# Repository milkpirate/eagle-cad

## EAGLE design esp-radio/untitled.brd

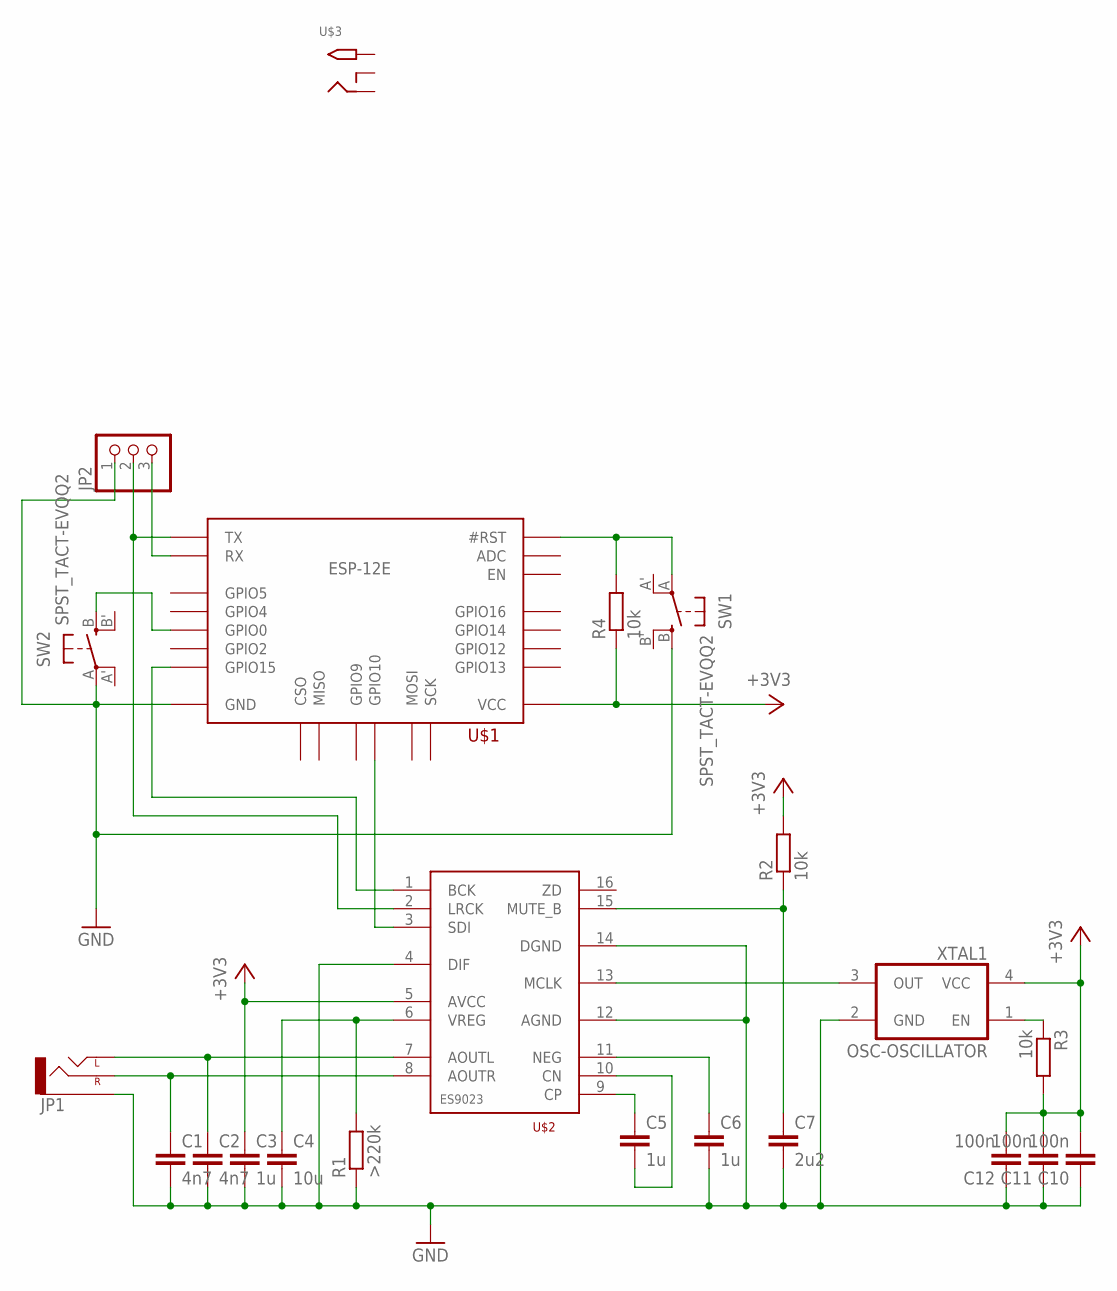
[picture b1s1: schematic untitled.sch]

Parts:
C1, C2: 4n7; C0805K
C3, C5, C6: 1u; C0805K
C4: 10u; C0805K
C7: 2u2; C0805K
C10, C11, C12: 100n; C0805K
JP1: AUDIO-JACKPIN-HOLES; AUDIO-JACK-HOLES
JP2: PINHD-1X3; 1X03
R1: >220k; M0805
R2, R3, R4: 10k; M0805
SW1, SW2: SPST_TACT-EVQQ2; EVQ-Q2
U$1: ESP-07/12_ESP-12E; ESP-07/12
U$2: ES9023-SMD; SOP16
U$3: 2.1MMJACKTHM; PJ-102A
XTAL1: OSC-OSCILLATOR; OSCILLATOR_7X5_SMD

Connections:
+3V3: C3.1, C10.2, C11.2, C12.2, R2.2, R3.2, R4.1, U$1.VCC, U$2.5 (AVCC), XTAL1.4 (VCC)
GND: C1.2, C2.2, C3.2, C4.2, C6.2, C7.2, C10.1, C11.1, C12.1, JP1.GND (SLEEVE), JP2.1, R1.1, SW1.B (S), SW2.A, U$1.GND, U$2.4 (DIF), U$2.12 (AGND), U$2.14 (DGND), XTAL1.2 (GND)
unnamed: R3.1, XTAL1.1 (EN)
unnamed: R4.2, SW1.A, U$1.REST (#RST)
unnamed: C4.1, R1.2, U$2.6 (VREG)
unnamed: C5.1, U$2.9 (CP)
unnamed: C5.2, U$2.10 (CN)
unnamed: C6.1, U$2.11 (NEG)
unnamed: C7.1, R2.1, U$2.15 (MUTE_B)
unnamed: SW2.B (S), U$1.GPIO0
unnamed: U$1.GPIO15, U$2.1 (BCK)
unnamed: C1.1, JP1.R+ (RIGHT), U$2.8 (AOUTR)
unnamed: C2.1, JP1.L1- (LEFT), JP1.L2- (LEFT), U$2.7 (AOUTL)
unnamed: JP2.2, U$1.TXD0 (TX), U$2.2 (LRCK)
unnamed: JP2.3, U$1.RXD0 (RX)
unnamed: U$1.GPIO10, U$2.3 (SDI)
unnamed: U$2.13 (MCLK), XTAL1.3 (OUT)

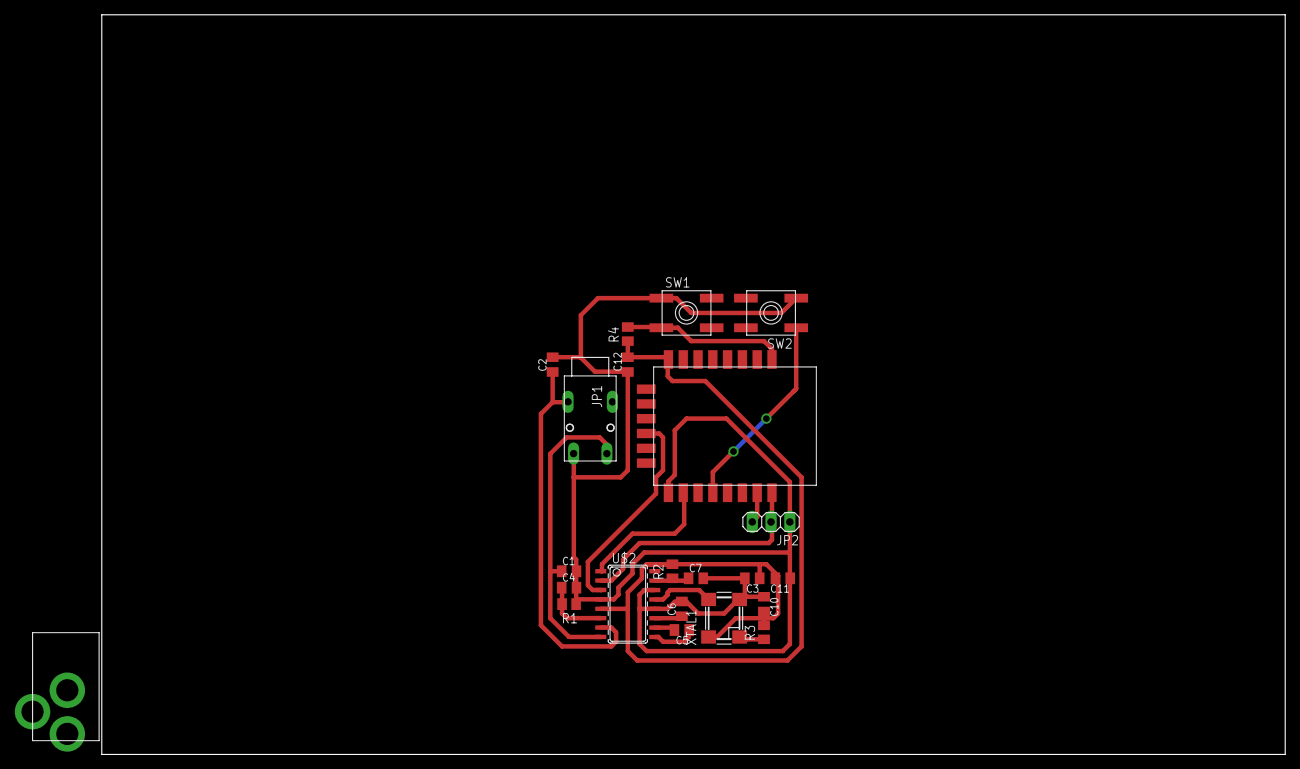
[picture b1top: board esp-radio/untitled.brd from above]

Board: 2 copper layers, 160.0 x 100.0 mm, 22 parts (0 on the bottom side), 17 nets.

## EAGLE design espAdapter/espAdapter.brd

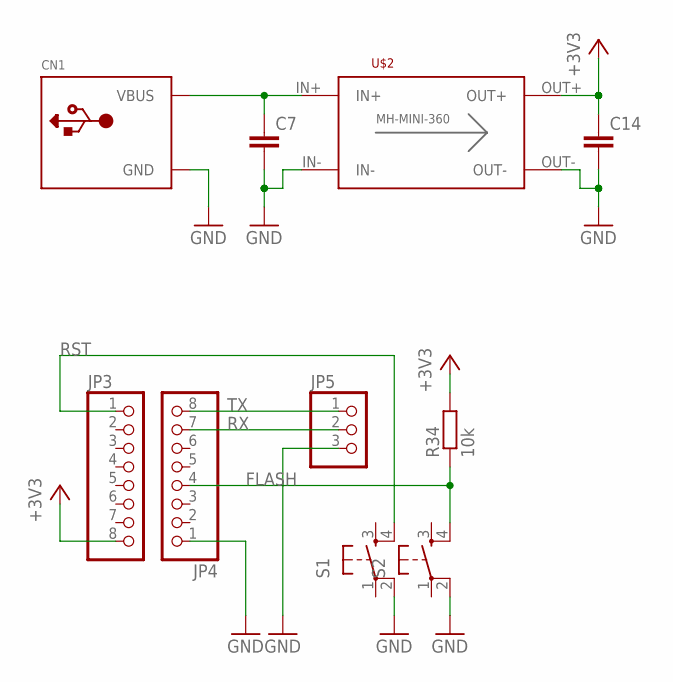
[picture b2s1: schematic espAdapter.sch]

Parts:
C7, C14: C-EU025-025X050; C025-025X050
CN1: USBPWR-ONLY; USB-MINIB-THM
JP3, JP4: PINHD-1X8; 1X08
JP5: PINHD-1X3; 1X03
R34: 10k; 0204/7
S1, S2: TAC_SWITCHPTH; TACTILE-PTH
U$2: DC-DC_CONV_MINISTD; DC-DC_CONV_MINI

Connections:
+3V3: C14.1, JP3.8, R34.2, U$2.OUT+
FLASH: JP4.4, R34.1, S2.4
GND: C7.2, C14.2, CN1.GND, CN1.GND1 (GND), CN1.GND2 (GND), CN1.GND3 (GND), CN1.GND4 (GND), JP4.1, JP5.3, S1.2, S2.2, U$2.IN-, U$2.OUT-
unnamed: C7.1, CN1.VBUS, U$2.IN+
RST: JP3.1, S1.4
RX: JP4.7, JP5.2
TX: JP4.8, JP5.1

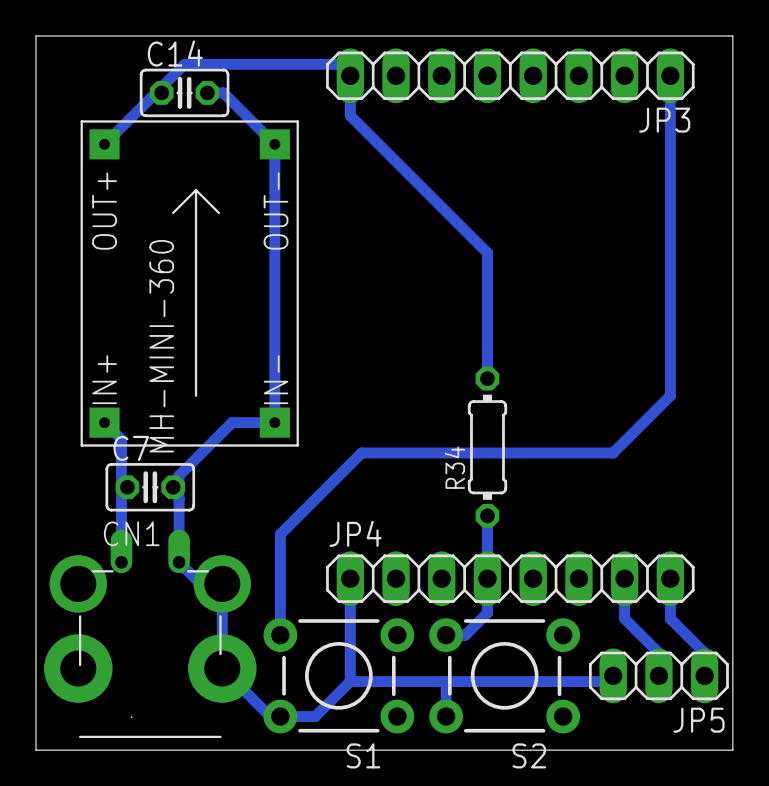
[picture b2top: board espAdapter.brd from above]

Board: 2 copper layers, 38.7 x 39.7 mm, 10 parts (0 on the bottom side), 7 nets.

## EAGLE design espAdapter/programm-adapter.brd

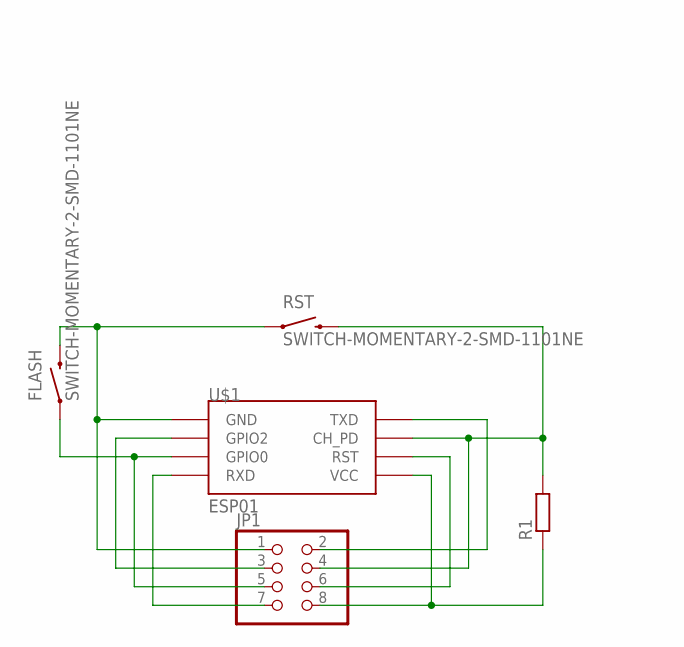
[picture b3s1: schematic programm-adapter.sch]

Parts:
FLASH: SWITCH-MOMENTARY-2-SMD-1101NE; TACTILE-SWITCH-1101NE
JP1: PINHD-2X4; 2X04
R1: R-EU_M0805; M0805
RST: SWITCH-MOMENTARY-2-SMD-1101NE; TACTILE-SWITCH-1101NE
U$1: ESP01

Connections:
GND: FLASH.2, JP1.1, RST.1, U$1.GND
unnamed: JP1.6, U$1.RST
unnamed: JP1.4, R1.2, RST.2, U$1.CH_PD
unnamed: JP1.2, U$1.TX (TXD)
unnamed: JP1.7, U$1.RX (RXD)
unnamed: FLASH.1, JP1.5, U$1.GPIO0
unnamed: JP1.3, U$1.GPIO2
VCC: JP1.8, R1.1, U$1.VCC

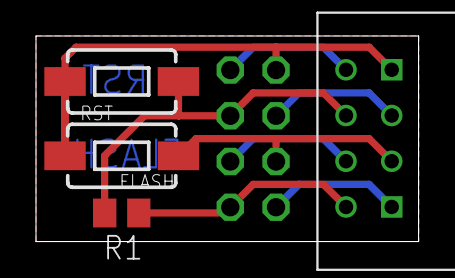
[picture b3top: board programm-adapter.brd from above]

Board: 2 copper layers, 21.3 x 11.4 mm, 5 parts (1 on the bottom side), 8 nets.

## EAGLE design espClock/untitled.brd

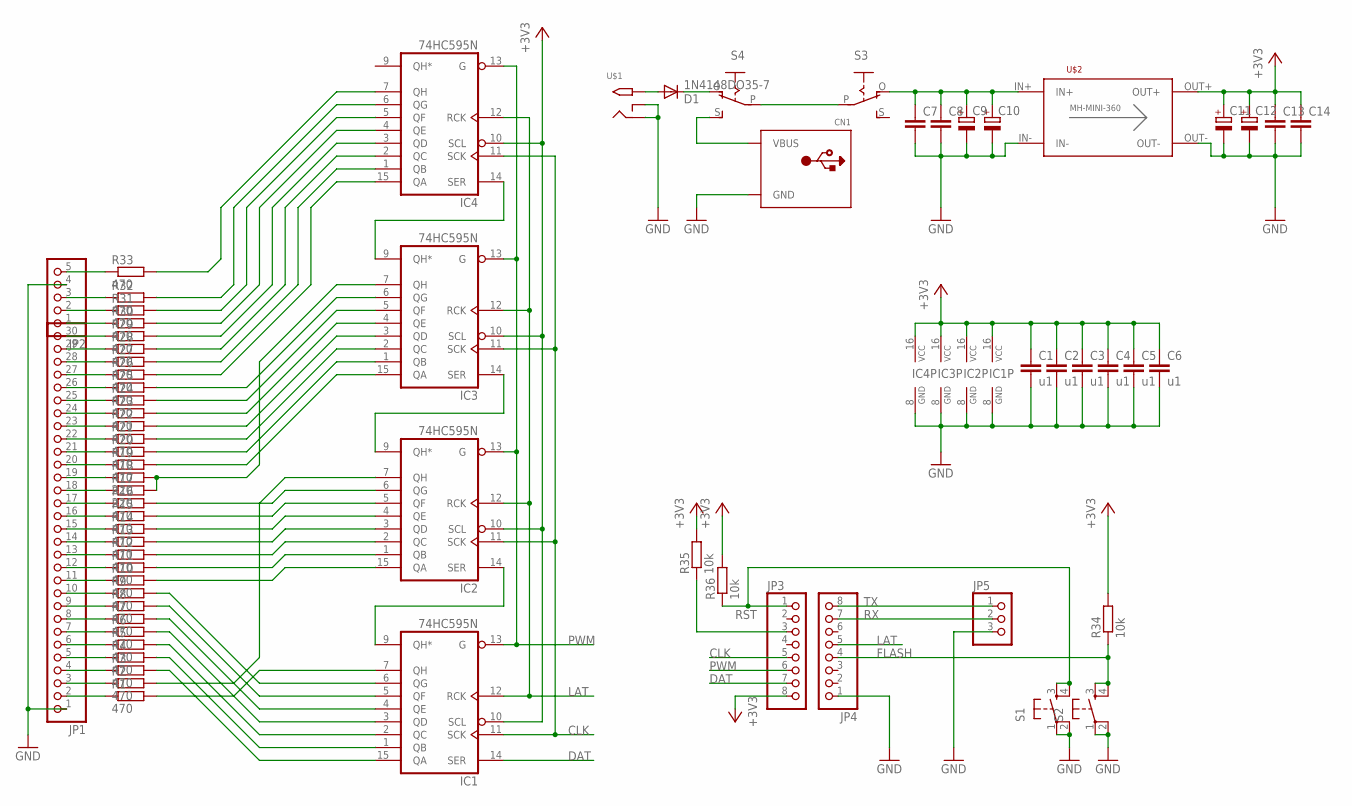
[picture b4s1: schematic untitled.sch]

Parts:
C1, C2, C3, C4, C5, C6: u1; C025-025X050
C7, C8, C13, C14: C-EU025-025X050; C025-025X050
C9, C10, C11, C12: CPOL-EUE2.5-7; E2,5-7
CN1: USBPWR-ONLY; USB-MINIB-THM
D1: 1N4148DO35-7; DO35-7
IC1, IC2, IC3, IC4: 74HC595N; DIL16
JP1: PINHD-1X30; 1X30
JP2: PINHD-1X5; 1X05
JP3, JP4: PINHD-1X8; 1X08
JP5: PINHD-1X3; 1X03
R1, R2, R3, R4, R5, R6, R7, R8, R9, R10, R11, R12, R13, R14, R15, R16, R19, R20, R21, R22, R23, R24, R25, R26, R27, R28, R29, R30, R31, R32, R33: 470; 0204/5
R17, R18: 220; 0204/5
R34: 10k; 0204/7
R35, R36: 10k; 0207/10
S1, S2: TAC_SWITCHPTH; TACTILE-PTH
S3, S4: EG1218S; EG1218
U$1: 2.1MMJACKTHM; PJ-102A
U$2: DC-DC_CONV_MINISTD; DC-DC_CONV_MINI

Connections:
+3V3: C1.1, C2.1, C3.1, C4.1, C5.1, C6.1, C11.+, C12.+, C13.1, C14.1, IC1.10 (SCL), IC1.16 (VCC), IC2.10 (SCL), IC2.16 (VCC), IC3.10 (SCL), IC3.16 (VCC), IC4.10 (SCL), IC4.16 (VCC), JP3.8, R34.2, R35.2, R36.2, U$2.OUT+
CLK: IC1.11 (SCK), IC2.11 (SCK), IC3.11 (SCK), IC4.11 (SCK), JP3.5
DAT: IC1.14 (SER), JP3.7
FLASH: JP4.4, R34.1, S2.3, S2.4
GND: C1.2, C2.2, C3.2, C4.2, C5.2, C6.2, C7.2, C8.2, C9.-, C10.-, C11.-, C12.-, C13.2, C14.2, CN1.GND, CN1.GND1 (GND), CN1.GND2 (GND), CN1.GND3 (GND), CN1.GND4 (GND), IC1.8 (GND), IC2.8 (GND), IC3.8 (GND), IC4.8 (GND), JP1.1, JP2.4, JP4.1, JP5.3, S1.1, S1.2, S2.1, S2.2, U$1.RING, U$1.RING_SW, U$2.IN-, U$2.OUT-
LAT: IC1.12 (RCK), IC2.12 (RCK), IC3.12 (RCK), IC4.12 (RCK), JP4.5
unnamed: JP1.3, R2.1
unnamed: JP1.2, R1.1
unnamed: JP1.4, R3.1
unnamed: JP1.5, R4.1
unnamed: JP1.6, R5.1
unnamed: JP1.7, R6.1
unnamed: JP1.8, R7.1
unnamed: JP1.9, R8.1
unnamed: JP1.10, R9.1
unnamed: JP1.11, R10.1
unnamed: JP1.12, R11.1
unnamed: JP1.13, R12.1
unnamed: JP1.14, R13.1
unnamed: JP1.15, R14.1
unnamed: JP1.16, R15.1
unnamed: JP1.17, R16.1
unnamed: JP1.18, R17.1
unnamed: JP1.19, R18.1
unnamed: JP1.20, R19.1
unnamed: JP1.21, R20.1
unnamed: JP1.22, R21.1
unnamed: JP1.23, R22.1
unnamed: JP1.24, R23.1
unnamed: JP1.25, R24.1
unnamed: JP1.26, R25.1
unnamed: JP1.27, R26.1
unnamed: JP1.28, R27.1
unnamed: JP1.29, R28.1
unnamed: IC4.15 (QA), R26.2
unnamed: IC1.9 (QH*), IC2.14 (SER)
unnamed: IC2.9 (QH*), IC3.14 (SER)
unnamed: IC3.9 (QH*), IC4.14 (SER)
unnamed: IC1.7 (QH), R1.2
unnamed: IC1.15 (QA), R3.2
unnamed: IC1.1 (QB), R4.2
unnamed: IC1.2 (QC), R5.2
unnamed: IC1.3 (QD), R6.2
unnamed: IC1.4 (QE), R7.2
unnamed: IC1.5 (QF), R8.2
unnamed: IC1.6 (QG), R9.2
unnamed: IC2.7 (QH), R2.2
unnamed: IC2.15 (QA), R10.2
unnamed: IC2.1 (QB), R11.2
unnamed: IC2.2 (QC), R12.2
unnamed: IC2.3 (QD), R13.2
unnamed: IC2.4 (QE), R14.2
unnamed: IC2.5 (QF), R15.2
unnamed: IC2.6 (QG), R16.2
unnamed: IC4.1 (QB), R27.2
unnamed: IC3.15 (QA), R19.2
unnamed: IC3.1 (QB), R20.2
unnamed: IC3.2 (QC), R21.2
unnamed: IC3.3 (QD), R22.2
unnamed: IC3.4 (QE), R23.2
unnamed: IC3.5 (QF), R24.2
unnamed: IC3.6 (QG), R25.2
unnamed: JP1.30, R29.1
unnamed: JP2.1, R30.1
unnamed: JP2.2, R31.1
unnamed: JP2.3, R32.1
unnamed: JP2.5, R33.1
unnamed: IC3.7 (QH), R17.2, R18.2
unnamed: IC4.2 (QC), R28.2
unnamed: IC4.3 (QD), R29.2
unnamed: IC4.4 (QE), R30.2
unnamed: IC4.5 (QF), R31.2
unnamed: IC4.6 (QG), R32.2
unnamed: IC4.7 (QH), R33.2
unnamed: JP3.3, R35.1
unnamed: D1.A, U$1.TIP
unnamed: C7.1, C8.1, C9.+, C10.+, S3.O, U$2.IN+
unnamed: S3.P, S4.P
unnamed: CN1.VBUS, S4.S
unnamed: D1.C, S4.O
PWM: IC1.13 (G), IC2.13 (G), IC3.13 (G), IC4.13 (G), JP3.6
RST: JP3.1, R36.1, S1.3, S1.4
RX: JP4.7, JP5.2
TX: JP4.8, JP5.1

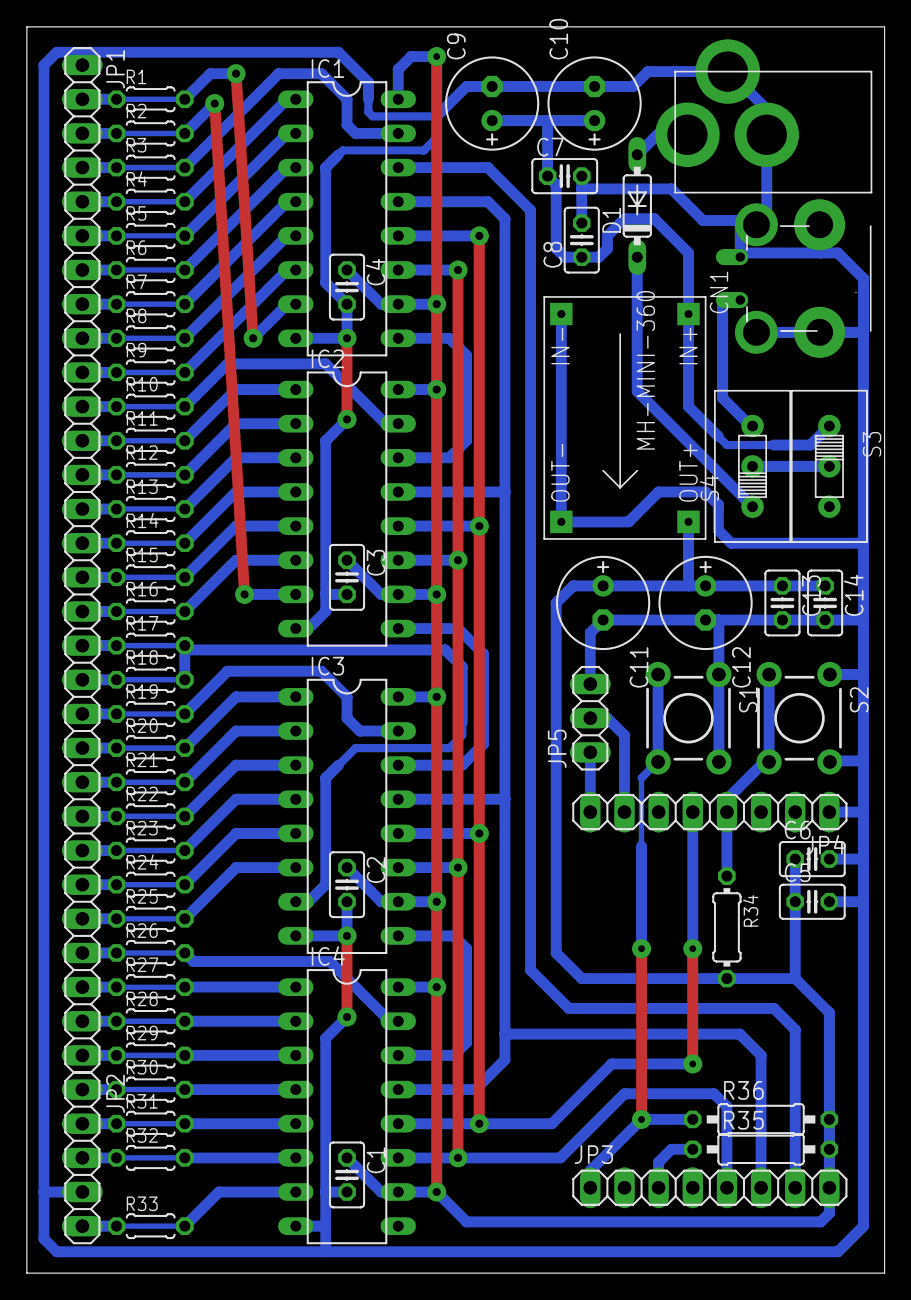
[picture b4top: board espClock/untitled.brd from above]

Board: 2 copper layers, 63.8 x 92.7 mm, 67 parts (0 on the bottom side), 84 nets.

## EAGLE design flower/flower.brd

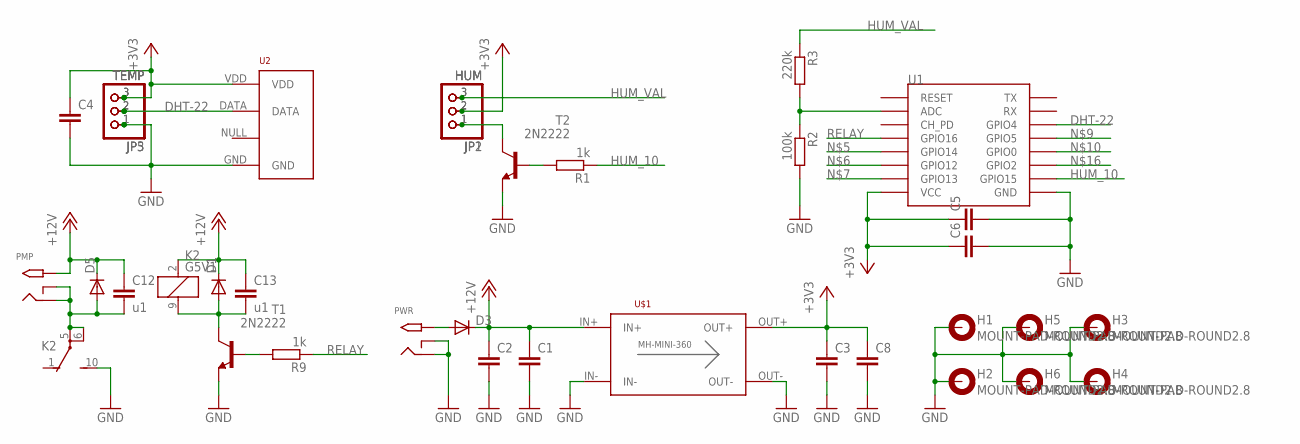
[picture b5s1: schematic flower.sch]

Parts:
C1, C3, C4, C5, C6: C-EU025-025X050; C025-025X050
C2, C8: C-EUC0805K; C0805K
C12, C13: u1; C025-025X050
D1, D3, D5: DIODE-D-5; D-5
H1, H2, H3, H4, H5, H6: MOUNT-PAD-ROUND2.8; 2,8-PAD
JP1: HUM; 1X03/90
JP2: HUM; 1X03
JP3: TEMP; 1X03
JP5: TEMP; 1X03/90
K2: G5V1
PMP: PMP; PJ-102A
PWR: PWR; PJ-102A
R1: 1k; 0204/7
R2: 100k; 0204/7
R3: 220k; 0204/7
R9: 1k; 0207/10
T1, T2: 2N2222; TO92-EBC-OVAL
U1: ESP12EDIP; ESP-12-BREAKOUT
U2: RHT03_DHT-22_AM2302RA; RHT03_DHT-22/RA
U$1: DC-DC_CONV_MINISTD; DC-DC_CONV_MINI

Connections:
+3V3: C3.1, C4.1, C5.1, C6.1, C8.1, JP1.2, JP2.2, JP3.3, JP5.3, U1.P$1 (VCC), U2.VDD, U$1.OUT+
+12V: C1.1, C2.1, C12.1, C13.1, D1.C, D3.C, D5.C, K2.2 (1), PMP.TIP, U$1.IN+
DHT-22: JP3.2, JP5.2, U1.P$14 (GPIO4), U2.DATA
GND: C1.2, C2.2, C3.2, C4.2, C5.2, C6.2, C8.2, H1.B2,8, H2.B2,8, H3.B2,8, H4.B2,8, H5.B2,8, H6.B2,8, JP3.1, JP5.1, K2.10 (S), PWR.RING, PWR.RING_SW, R2.2, T1.E, T2.E, U1.P$9 (GND), U2.GND, U$1.IN-, U$1.OUT-
HUM_10: R1.1, U1.P$10 (GPIO15)
HUM_VAL: JP1.3, JP2.3, R3.1
unnamed: R1.2, T2.B
unnamed: JP1.1, JP2.1, T2.C
unnamed: R2.1, R3.2, U1.P$7 (ADC)
unnamed: C12.2, D5.A, K2.5, K2.6, PMP.RING, PMP.RING_SW
unnamed: D3.A, PWR.TIP
unnamed: C13.2, D1.A, K2.9 (2), T1.C
unnamed: R9.2, T1.B
RELAY: R9.1, U1.P$5 (GPIO16)

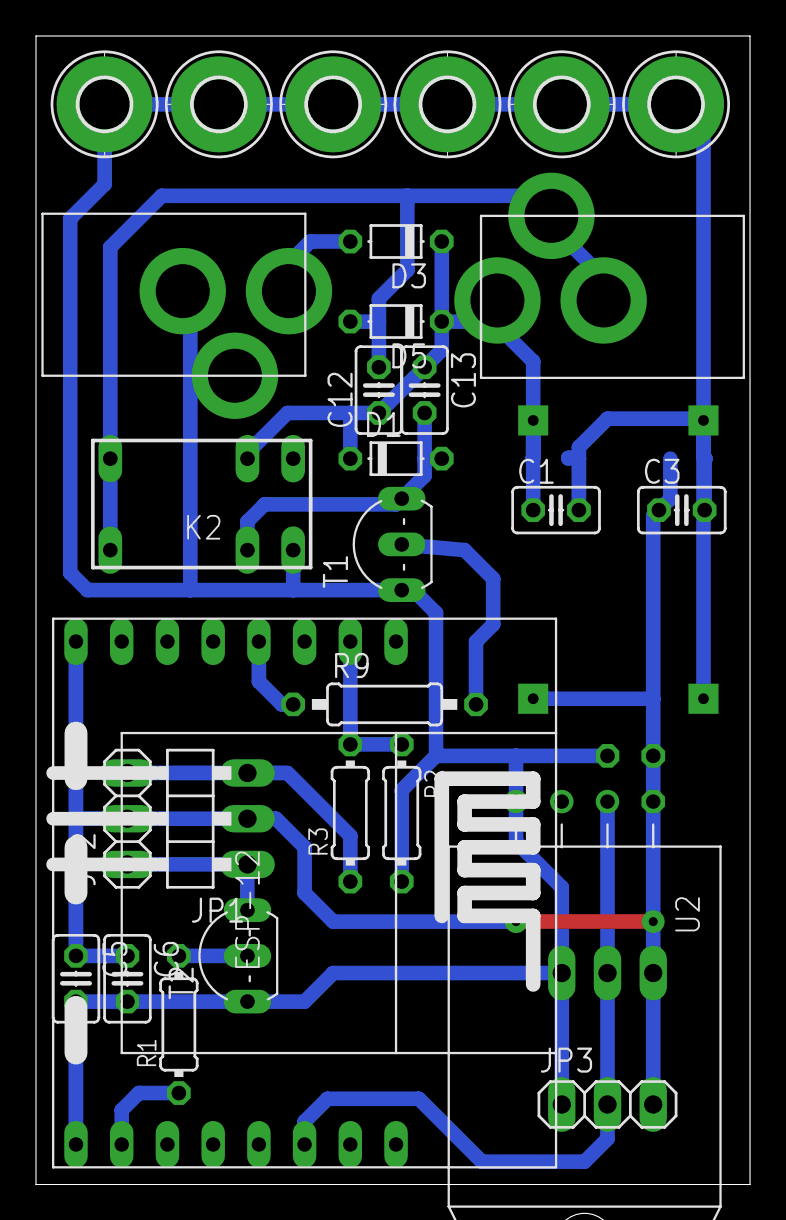
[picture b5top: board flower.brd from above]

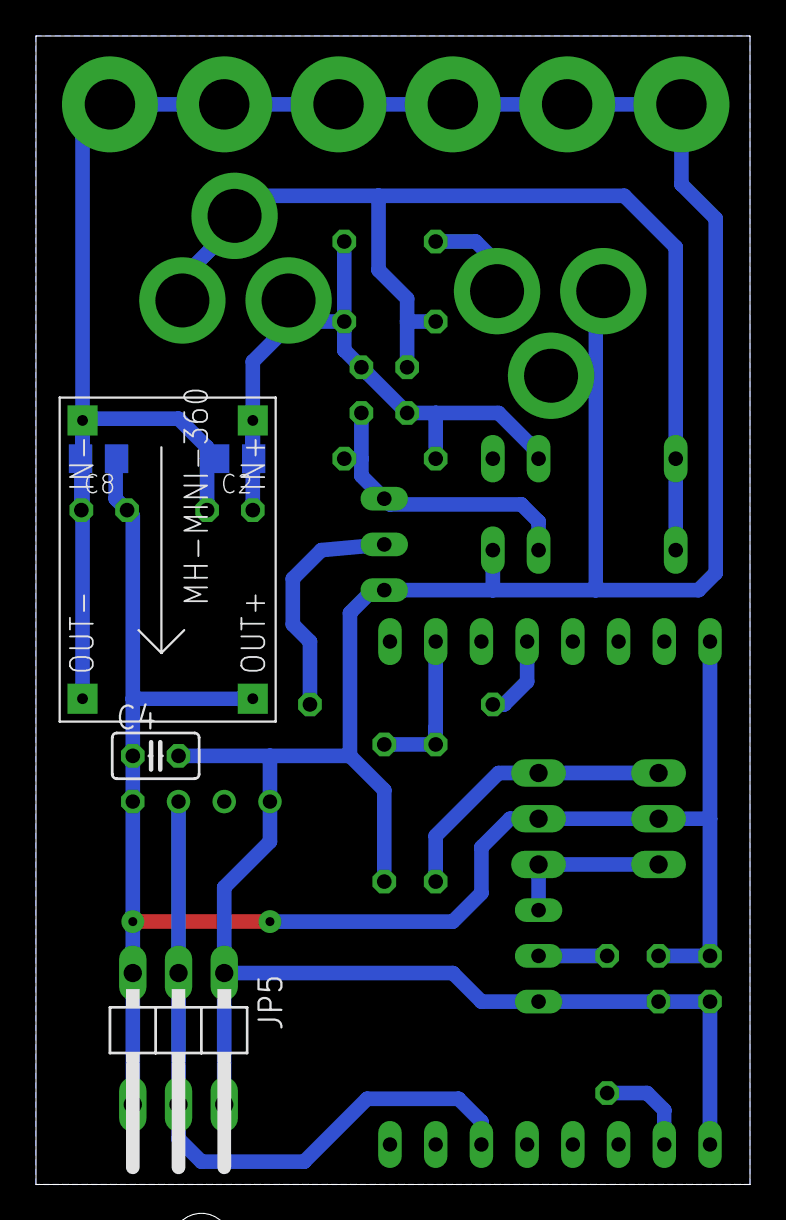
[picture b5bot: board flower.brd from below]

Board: 2 copper layers, 39.7 x 63.8 mm, 34 parts (5 on the bottom side), 14 nets.

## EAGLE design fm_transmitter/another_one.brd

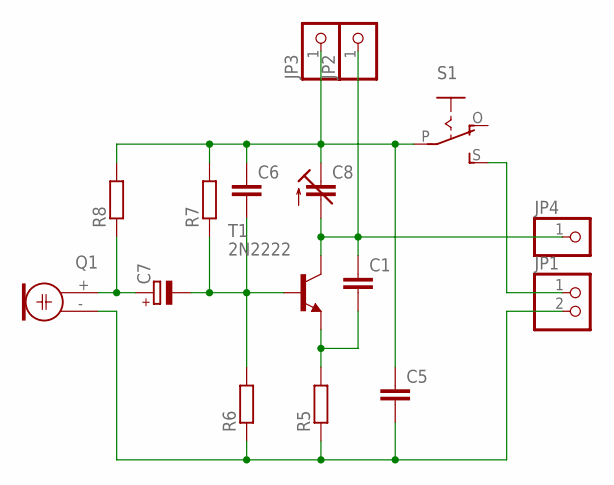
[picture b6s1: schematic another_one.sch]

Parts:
C1, C5, C6: C-EU025-025X050; C025-025X050
C7: CPOL-EUE2,5-6E; E2,5-6E
C8: C-TRIMM808; CTRIM808-BC
JP1: PINHD-1X2; 1X02
JP2, JP3, JP4: PINHD-1X1CB; 1X01-CLEANBIG
Q1: ELECTRET; 9.7ELECTRET
R5: R-EU_0204/5; 0204/5
R6, R7, R8: R-EU_0207/2V; 0207/2V
S1: EG1218S; EG1218
T1: 2N2222; TO92-EBC-OVAL

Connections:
unnamed: C7.+, Q1.+ (2), R8.1
unnamed: C6.2, C7.-, R6.2, R7.1, T1.B
unnamed: C1.2, R5.2, T1.E
unnamed: C5.2, JP1.2, Q1.- (1), R5.1, R6.1
unnamed: C5.1, C6.1, C8.1 (E), JP3.1, R7.2, R8.2, S1.P
unnamed: C1.1, C8.2 (A), JP2.1, JP4.1, T1.C
unnamed: JP1.1, S1.S

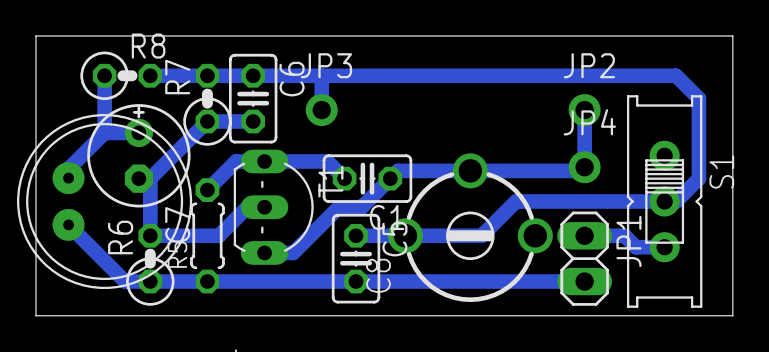
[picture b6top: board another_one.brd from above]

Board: 2 copper layers, 38.7 x 15.5 mm, 16 parts (0 on the bottom side), 7 nets.

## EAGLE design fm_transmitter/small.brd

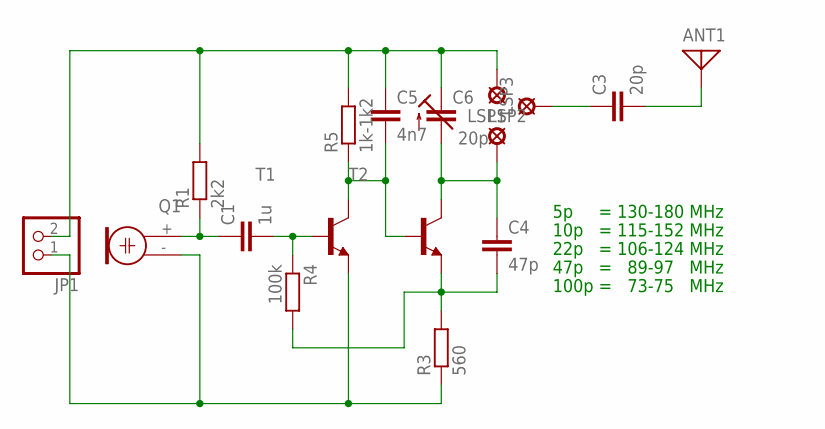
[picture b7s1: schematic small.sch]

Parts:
ANT1: ANTENNA; PAD-01
C1: 1u; C025-025X050
C3: 20p; C025-025X050
C4: 47p; C025-025X050
C5: 4n7; C025-025X050
C6: 20p; CTRIM808-BC
JP1: PINHD-1X2; 1X02
LSP1, LSP2, LSP3: SE14
Q1: ELECTRET; 9.7ELECTRET
R1: 2k2; 0207/2V
R3: 560; 0207/2V
R4: 100k; 0207/2V
R5: 1k-1k2; 0207/2V
T1, T2: BC547-NPN-TO92-CBE; TO92-CBE

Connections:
GND: JP1.1, Q1.- (1), R3.1, T1.E
unnamed: C1.1, Q1.+ (2), R1.1
unnamed: C1.2, R4.1, T1.B
unnamed: C4.2, R3.2, R4.2, T2.E
unnamed: C5.2, R5.1, T1.C, T2.B
unnamed: C4.1, C6.2 (A), LSP2.MP, T2.C
unnamed: C3.1, LSP3.MP
unnamed: C5.1, C6.1 (E), JP1.2, LSP1.MP, R1.2, R5.2
unnamed: ANT1.1, C3.2

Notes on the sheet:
5p = 130-180 MHz
10p = 115-152 MHz
22p = 106-124 MHz
47p = 89-97 MHz
100p = 73-75 MHz

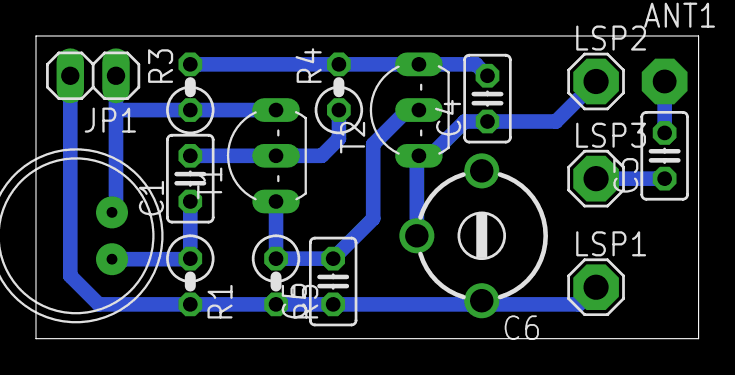
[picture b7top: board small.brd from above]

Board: 2 copper layers, 36.8 x 16.8 mm, 17 parts (0 on the bottom side), 9 nets.

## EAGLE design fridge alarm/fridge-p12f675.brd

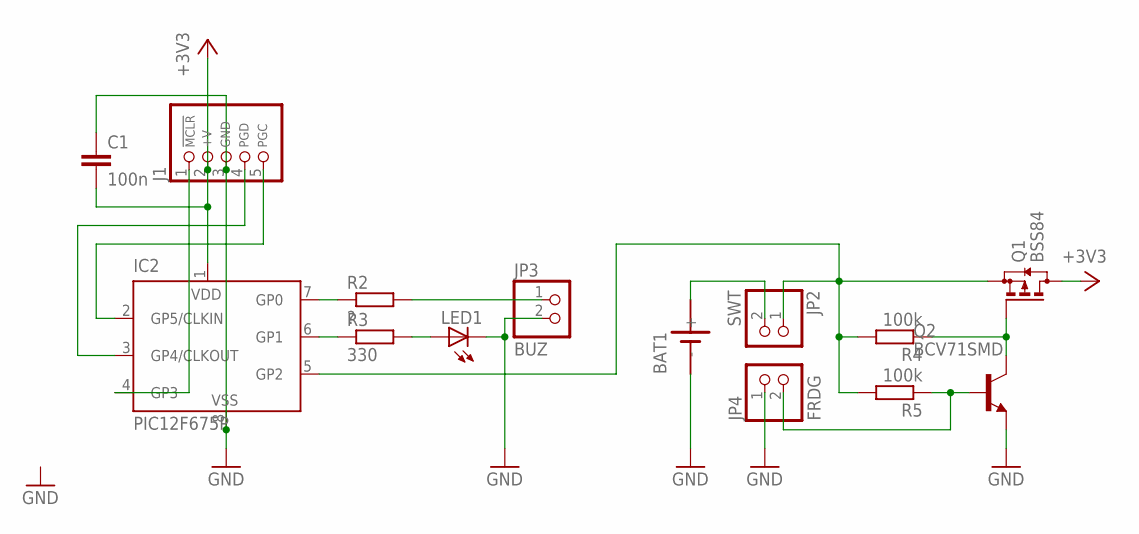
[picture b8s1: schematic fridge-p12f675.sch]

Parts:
BAT1: SN2032
C1: 100n; C0805K
IC2: PIC12F675P; DIL8
J1: CON_HEADER_PRG_PIC_ICSP0.1INCH_A; HEADER_PRG_1X05
JP2: SWT; 1X02
JP3: BUZ; 1X02
JP4: FRDG; 1X02
LED1: LEDCHIPLED_0805; CHIPLED_0805
Q1: BSS84; SOT23
Q2: BCV71SMD; SOT23-BEC
R2: ?; R0805
R3: 330; R0805
R4, R5: 100k; R0805

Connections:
+3V3: C1.2, IC2.1 (VDD), J1.2 (+V), Q1.3 (D)
GND: BAT1.-, C1.1, IC2.8 (VSS), J1.3 (GND), JP3.2, JP4.1, LED1.C, Q2.E
unnamed: BAT1.+, JP2.2
unnamed: IC2.7 (GP0), R2.1
unnamed: IC2.6 (GP1), R3.1
unnamed: LED1.A, R3.2
unnamed: JP3.1, R2.2
unnamed: IC2.5 (GP2), JP2.1, Q1.2 (S), R4.2, R5.2
unnamed: JP4.2, Q2.B, R5.1
unnamed: Q1.1 (G), Q2.C, R4.1
unnamed: IC2.2 (GP5/CLKIN), J1.5 (PGC)
unnamed: IC2.3 (GP4/CLKOUT), J1.4 (PGD)
unnamed: IC2.4 (GP3), J1.1 (/MCLR)

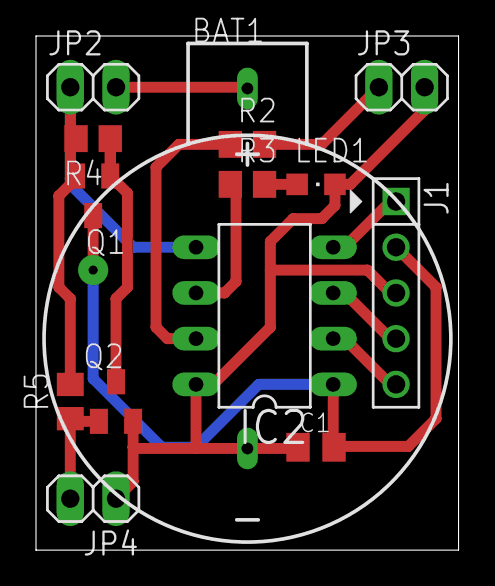
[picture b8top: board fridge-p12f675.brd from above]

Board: 2 copper layers, 23.5 x 28.6 mm, 14 parts (0 on the bottom side), 13 nets.

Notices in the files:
parts and their libraries:
SparkFun-Electromechanical: Licensing: Creative Commons ShareAlike 4.0 International - https://creativecommons.org/licenses/by-sa/4.0
